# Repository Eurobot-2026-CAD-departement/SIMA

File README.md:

# SIMA

CAD and electronics for the **SIMA** and **PAMI** robots and related designs.

## Contents
- `PAMI 3.0/`, `PAMI 3.0 final/`, `PAMI finalll/` — PAMI iterations (the largest assembly, `PAMIIII.SLDASM`, is stored with Git LFS), including base, cover, mechanism support and 3D printing files
- `SIMA container/`, `SIMA arrangement/` — SIMA container and arrangement/support parts
- `sheild esp pami ninja/` — KiCad shield (ESP32) for the PAMI / Ninja
- `NINJA CAD/`, `ninja/` — Ninja robot CAD, `piece util`, gripper and cutting files
- `pami/` — PAMI parts (e.g. small encoder wheels)

---

Part of the CAD work of the **Aerobotix (INSAT, Tunisia) Eurobot 2026 team** — see the [organization](https://github.com/Eurobot-2026-CAD-departement) for the other repositories. Files are mainly SolidWorks (`.SLDPRT` / `.SLDASM`) with STEP / STL / DXF exports. Released under the [MIT License](LICENSE). Questions about anything unclear? Contact a team member.

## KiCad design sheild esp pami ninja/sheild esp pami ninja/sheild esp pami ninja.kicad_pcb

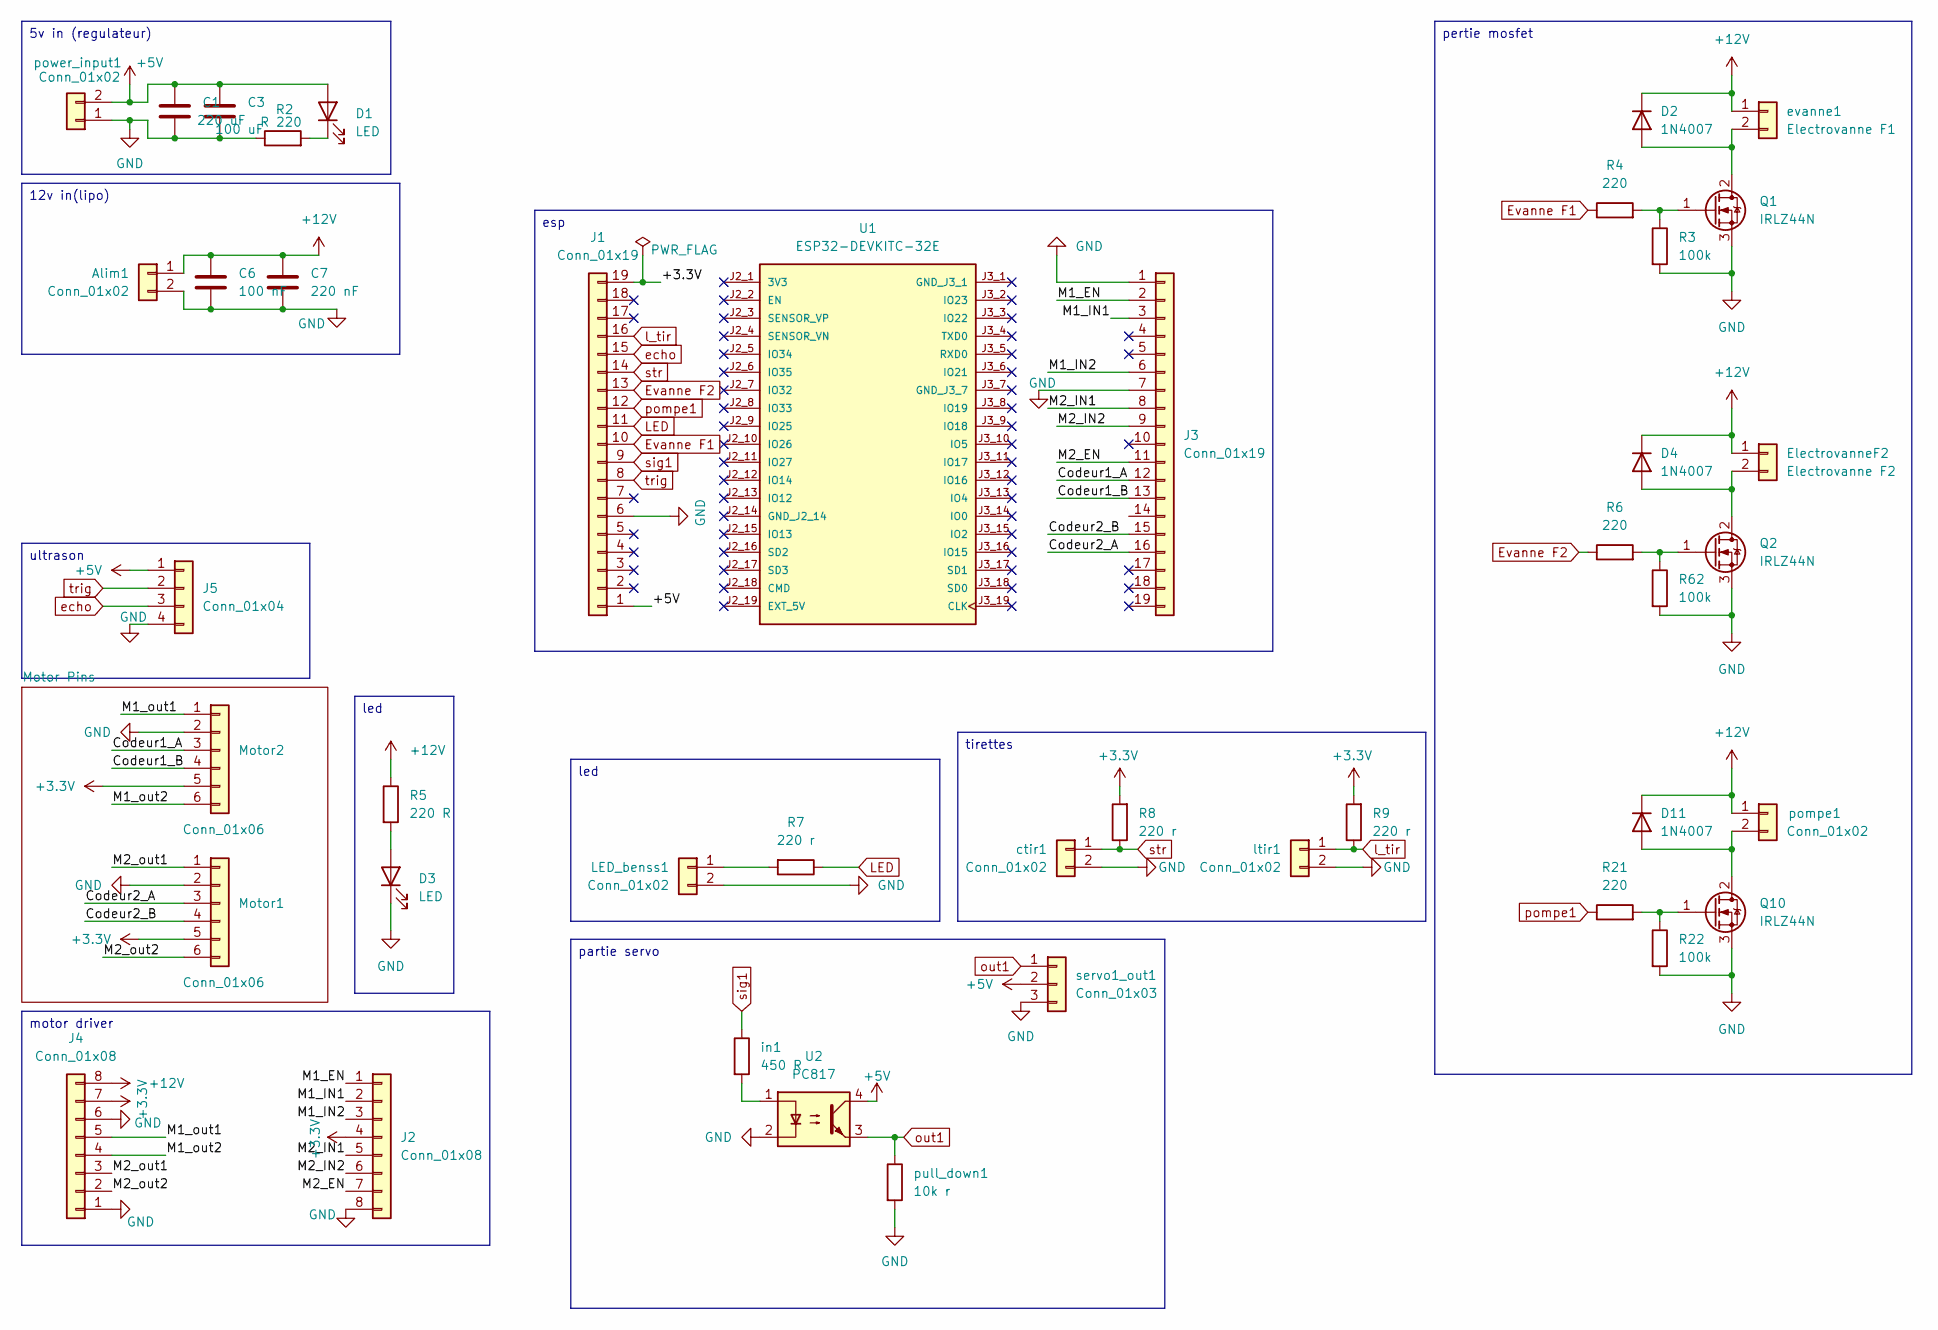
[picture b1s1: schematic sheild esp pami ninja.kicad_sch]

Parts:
Alim1: Conn_01x02; TerminalBlock_MaiXu_MX126-5.0-02P_1x02_P5.00mm
C1: 220 uF; C_Radial_D6.3mm_H5.0mm_P2.50mm
C3: 100 uF; C_Radial_D6.3mm_H5.0mm_P2.50mm
C6: 100 nF; C_Radial_D6.3mm_H5.0mm_P2.50mm
C7: 220 nF; C_Radial_D6.3mm_H5.0mm_P2.50mm
D1, D3: LED; LED_D4.0mm
D2, D4, D11: 1N4007; D_DO-41_SOD81_P10.16mm_Horizontal
ElectrovanneF2: Electrovanne F2; JST_XH_B2B-XH-A_1x02_P2.50mm_Vertical
J1, J3: Conn_01x19; PinSocket_1x19_P2.54mm_Vertical
J2, J4: Conn_01x08; PinSocket_1x08_P2.54mm_Vertical
J5: Conn_01x04; PinHeader_1x04_P2.54mm_Vertical
LED_benss1: Conn_01x02; PinHeader_1x02_P2.54mm_Vertical
Motor1, Motor2: Conn_01x06; PinHeader_1x06_P2.54mm_Vertical
Q1, Q2, Q10: IRLZ44N; TO-220-3_Vertical
R2: R 220; R_Axial_DIN0207_L6.3mm_D2.5mm_P7.62mm_Horizontal
R3, R22, R62: 100k; R_Axial_DIN0207_L6.3mm_D2.5mm_P7.62mm_Horizontal
R4, R6, R21: 220; R_Axial_DIN0207_L6.3mm_D2.5mm_P7.62mm_Horizontal
R5: 220 R; R_Axial_DIN0207_L6.3mm_D2.5mm_P7.62mm_Horizontal
R7, R8, R9: 220 r; R_Axial_DIN0207_L6.3mm_D2.5mm_P7.62mm_Horizontal
U1: ESP32-DEVKITC-32E; PARTREV 1.4
U2: PC817; DIP-4_W7.62mm
ctir1: Conn_01x02; PinHeader_1x02_P2.54mm_Vertical
evanne1: Electrovanne F1; JST_XH_B2B-XH-A_1x02_P2.50mm_Vertical
in1: 450 R; R_Axial_DIN0207_L6.3mm_D2.5mm_P7.62mm_Horizontal
ltir1: Conn_01x02; PinHeader_1x02_P2.54mm_Vertical
pompe1: Conn_01x02; JST_XH_B2B-XH-A_1x02_P2.50mm_Vertical
power_input1: Conn_01x02; TerminalBlock_MaiXu_MX126-5.0-02P_1x02_P5.00mm
pull_down1: 10k r; R_Axial_DIN0207_L6.3mm_D2.5mm_P7.62mm_Horizontal
servo1_out1: Conn_01x03; PinHeader_1x03_P2.54mm_Vertical

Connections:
+3.3V: J1.19, J2.4, J4.7, Motor1.5, Motor2.5, R8.2, R9.2
+5V: C1.1, C3.1, D1.2 (A), J1.1, J5.1, U2.4, power_input1.2, servo1_out1.2
+12V: Alim1.1, C6.1, C7.1, D2.1 (K), D4.1 (K), D11.1 (K), ElectrovanneF2.1, J4.8, R5.1, evanne1.1, pompe1.1
/Codeur1_A: J3.12, Motor2.3
/Codeur1_B: J3.13, Motor2.4
/Codeur2_A: J3.16, Motor1.3
/Codeur2_B: J3.15, Motor1.4
/M1_EN: J2.1, J3.2
/M1_IN1: J2.2, J3.3
/M1_IN2: J2.3, J3.6
/M1_out1: J4.5, Motor2.1
/M1_out2: J4.4, Motor2.6
/M2_EN: J2.7, J3.11
/M2_IN1: J2.5, J3.8
/M2_IN2: J2.6, J3.9
/M2_out1: J4.3, Motor1.1
/M2_out2: J4.2, Motor1.6
Evanne F1: J1.10, R4.1
Evanne F2: J1.13, R6.1
GND: Alim1.2, C1.2, C3.2, C6.2, C7.2, D3.1 (K), J1.6, J2.8, J3.1, J3.7, J4.1, J4.6, J5.4, LED_benss1.2, Motor1.2, Motor2.2, Q1.3 (S), Q2.3 (S), Q10.3 (S), R2.1, R3.2, R22.2, R62.2, U2.2, ctir1.2, ltir1.2, power_input1.1, pull_down1.2, servo1_out1.3
LED: J1.11, R7.1
unnamed: D1.1 (K), R2.2
unnamed: D2.2 (A), Q1.2 (D), evanne1.2
unnamed: D3.2 (A), R5.2
unnamed: D4.2 (A), ElectrovanneF2.2, Q2.2 (D)
unnamed: D11.2 (A), Q10.2 (D), pompe1.2
unnamed: LED_benss1.1, R7.2
unnamed: Q1.1 (G), R3.1, R4.2
unnamed: Q2.1 (G), R6.2, R62.1
unnamed: Q10.1 (G), R21.2, R22.1
unnamed: U2.1, in1.2
echo: J1.15, J5.3
l_tir: J1.16, R9.1, ltir1.1
out1: U2.3, pull_down1.1, servo1_out1.1
pompe1: J1.12, R21.1
sig1: J1.9, in1.1
str: J1.14, R8.1, ctir1.1
trig: J1.8, J5.2

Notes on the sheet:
esp
led
pertie mosfet
5v in (regulateur)
tirettes
ultrason
12v in(lipo)
partie servo
motor driver

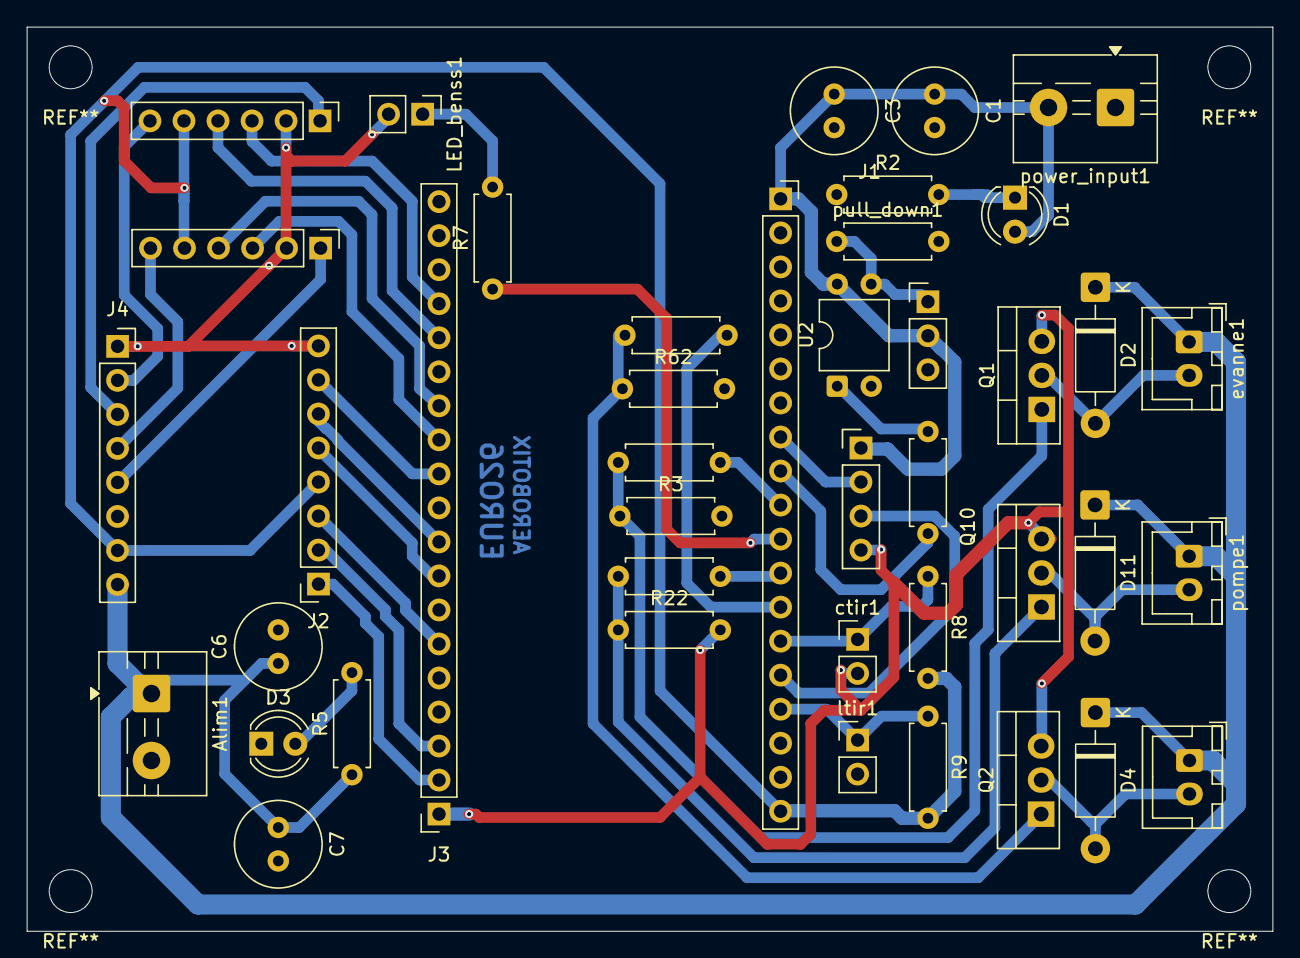
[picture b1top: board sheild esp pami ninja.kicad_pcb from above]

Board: 2 copper layers, 93.0 x 67.5 mm, 42 parts (0 on the bottom side), 38 nets.
